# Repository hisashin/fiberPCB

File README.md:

# Getting started with fiberPCB, Fiber Laser DIY PCB

- [Why fiberPCB?](#why-fiberPCB?)
- [References](#references)
- [Required tools and materials](#all-required-tools-and-materials)
- [How to choose fiber laser](#how-to-choose-fiber-laser)
- [How to choose laminator](#how-to-choose-laminator)
- [Detailed steps to make fiberPCB by KiCAD](#detailed-steps-to-make-fiberPCB-by-KiCAD)
- [Detailed steps to make fiberPCB by EAGLE](#detailed-steps-to-make-fiberPCB-by-EAGLE)

## Why fiberPCB?

Let's compare fiberPCB with alternatives.

* Online PCB service
  * Best way as long as you can wait delivery for few days to weeks.
  * Sometimes you cannot wait. In my case, PCB of [opensource Realtime PCR](https://github.com/hisashin/Ninja-qPCR) was so complex that I have to iterate orders to integrate functions like LED control, photosensing, multiplexing and ADC.
* Chemical etching
  * Cheap but need skills for small pitches like 10 mil (0.25mm).
  * Need to drill all holes and cut contor manually after etching.
  * Harmful to the environment.
* CNC milling
  * I had [$2300 CNC designed for PCB millling](https://www.youtube.com/watch?v=cwREOBL9E-A) and noticed that required time and cares are proportionate to the complexity of the pattern.
  * You must replace end mills not to cut holes and contor after cutting patterns. Or you have to replace it every 50 meter stroke. Machine with auto tool changer is expensive. [LPKF ProtoMat S104](https://www.youtube.com/watch?v=GRow5AqFxZA) is around $30,000.
  * To cut small pitches, you cannot engrave deeply. If depth is not enough, small copper partcle may bridge the gap. I'm totally fed up with such problems.
* Commercial PCB laser machine.
  * Ridiculously expensive. "Entry model" [LPKF Photolaser ST](https://www.youtube.com/watch?v=WMgXvRwbaLw) is over $100,000.
* CO2 Laser
  * I've never tried CO2 laser etching. Please send pull request if you can compare.
  * Cannot etch metal without spraying black.
  * Focal diameter is 100 times larger and edge might be unclear at small pitches.
  
## References
* [Making fine pitch PCB prototypes with fiber laser](https://www.kurokesu.com/main/2021/01/07/making-fine-pitch-pcb-prototypes-with-fiber-laser/?fbclid=IwAR3_8MipkpVS9d9DjpUQ1I7AqjXdvbW7uQoy86yiT56GoPLZ7w0Zegjyjy0)
* [Youtubes](https://www.youtube.com/playlist?list=PLIcr1mnww28Doh5sBvfblVOn0Wxk1qtYr)
 
## All required tools and materials
* Gerber Files (Free)
* [FlatCAM](http://flatcam.org/), Gerver->CAM conveter

  Latest stable FlatCAM3.5 needs Python2.7. Beta supports Python3 but crush often on Linux. [Pip](https://pypi.org/project/flatcam/#description) install looks easy but crushed while saving projects. I recommend to use Windows or Docker Ubuntu Desktop.
  
  - [Download](https://bitbucket.org/jpcgt/flatcam/downloads/) latest installer for Windows.
  - For Linux, [dorowu/ubuntu-desktop-lxde-vnc:release-v1.2](https://hub.docker.com/layers/dorowu/ubuntu-desktop-lxde-vnc/release-v1.2/images/sha256-54af3af44929d8337562448a122f32ce3ba35d8ae9aefe1365f1660d84b1792a?context=explore) is easiest.
  
   ```
   // Run this command in your terminal
   docker run -d -v (where you exported gerbers):/gerbers -v (somewhere to save flatcam projects):/projects -it --name flatcam -p 6080:80 -p 5901:5900  -e VNC_PASSWORD=password -v /dev/shm:/dev/shm dorowu/ubuntu-desktop-lxde-vnc:release-v1.2
   // My case
   docker run -d -v ~/github/fiberPCB/kicad/fiberPCB:/gerbers -v ~/github/fiberPCB/flatcam:/projects -it --name flatcam -p 6080:80 -p 5901:5900  -e VNC_PASSWORD=password -v /dev/shm:/dev/shm dorowu/ubuntu-desktop-lxde-vnc:release-v1.2
   
   // Connect VNC to vnc://localhost:5901, run these commands in Ubuntu terminal not yours.
   apt-get -y update
   apt-get -y install sudo wget git unzip
    
   //git clone https://bitbucket.org/jpcgt/flatcam <- it was also 3.5 when I tried on 2021 Jan 25
   wget https://bitbucket.org/jpcgt/flatcam/downloads/FlatCAM-8.5.zip
   unzip FlatCAM-8.5.zip
   cd FlatCAM-8.5
   sh setup_ubuntu.sh
   python FlatCAM.py
   ```

  - [dorowu/ubuntu-desktop-lxde-vnc](https://hub.docker.com/r/dorowu/ubuntu-desktop-lxde-vnc/):latest --- I couldn't install python-qt4.
  - [queeno/docker-ubuntu-desktop](https://github.com/queeno/docker-ubuntu-desktop):latest. --- It worked but app resolution was lowest.
  - Want to try FlatCAM nightly build in Python3? Here is how to install.
  
   ```
   python3 -V (3.5)
   // It was 3.5 for me and upgrade to 3.8 was needed in later step. skip here if yours is 3.8
   add-apt-repository ppa:deadsnakes/ppa
   apt-get -y update
   apt-get -y install python3.8
   update-alternatives --install /usr/bin/python3 python3 /usr/bin/python3.5 1
   update-alternatives --install /usr/bin/python3 python3 /usr/bin/python3.8 2
   update-alternatives --config python3 (Choose python3.8)
   python3 -V
   apt install -y python3.8-distutils python-setuptools python3-pip
   pip3 -V (8.1.1)
   apt remove python3-pip
   python3.8 -m easy_install pip
   pip -V (21.0)
 
   apt-get -y update
   apt-get -y install python3-pip python-setuptools sudo wget
   wget https://bitbucket.org/jpcgt/flatcam/downloads/FlatCAM_beta_8.994_sources.zip
   unzip FlatCAM_beta_8.994_sources.zip
   cd FlatCAM_beta_8.994_sources
   sh setup_ubuntu.sh
   python3 FlatCAM.py
   ```
   
* [EZCAD](https://www.litlaser.com/ezcad), laser controller
* Fiber Laser
* Laminator
* UV illuminator
* Dry film
  * I first thought that Kapton film can replace it but that would be wrong.
* [FR-4](https://en.wikipedia.org/wiki/FR-4)

My case in Tokyo Japan :
| Item                | Price         | Shipping     | Comment |
| ------------------- |:-------------:| ------------:| ------------:|
| [Fiber Laser](https://www.aliexpress.com/item/32974751052.html?spm=a2g0s.9042311.0.0.65f44c4dIleBKp&fbclid=IwAR10NMvGiH47895B0QpRRJNL5SNHvLvtUy33UhqqUZfuPdR8BVw_eg-WCHc)         | $1,837.44     | $249.81 | 20W JPT 200x200mm DHL8-16days |
| [Laminator](https://www.lami-corporation.co.jp/archives/products/leon13dx/)           | $10.64        | $11.12       | Got $1800 worth one as junk. Replaced blown fuse:wink: |
| [UV illuminator](https://www.amazon.co.jp/gp/product/B07HFRDK3V/ref=ppx_yo_dt_b_asin_title_o02_s00?ie=UTF8&psc=1&fbclid=IwAR2NO4W7daOl4TgFSwwDDsZGD15Jek28WylPpzhUsRBBjHX5G8EQiuQLUwU)      | $4.73         | $0           | I will line them up for larger PCB |
| [Dry film](https://www.amazon.co.jp/gp/product/B01NCS88LU/ref=ppx_yo_dt_b_asin_title_o05_s01?ie=UTF8&psc=1&fbclid=IwAR3ORckfPM1z7tKVWN8LTQ-CgsBqjpBLfcwR8V2A0jhZy2ZhwNkz0N1GbfY)          | $19.15        | $0           | VANTIYAUS Zp00088(5m x 30cm) |
| [FR-4](https://www.sengoku.co.jp/mod/sgk_cart/detail.php?code=EEHD-4BPE)                | $1.64         | $0           | 1.6t x 75 x 100mm |
| Total               | $1873.6       | $260.93      |  $2395.46 include shippings |

## How to choose fiber laser
 // TODO Stronger/Wider is not always better

## How to choose laminator
 // TODO List confirmed to support 1.6mm thickness

## Detailed steps to make fiberPCB by KiCAD
 1. Design PCB as usual
   
 2. Export Gerber Files
   - **File/Plot** and check F.Cu, F.Paste, F.Mask and Edge.Cuts then **Plot**
   
   - **Generate Drill Files... / Generate Drill File**
   
 3. Convert Gerber
   - **File / Open Gerbers** and select all gerbers exported at prior step.
   
 4. Convert CAM
 5. Cut patterns
 6. Print solder mask
 7. Open pads
 8. Cut holes and contor

## Detailed steps to make fiberPCB by EAGLE

// TODO

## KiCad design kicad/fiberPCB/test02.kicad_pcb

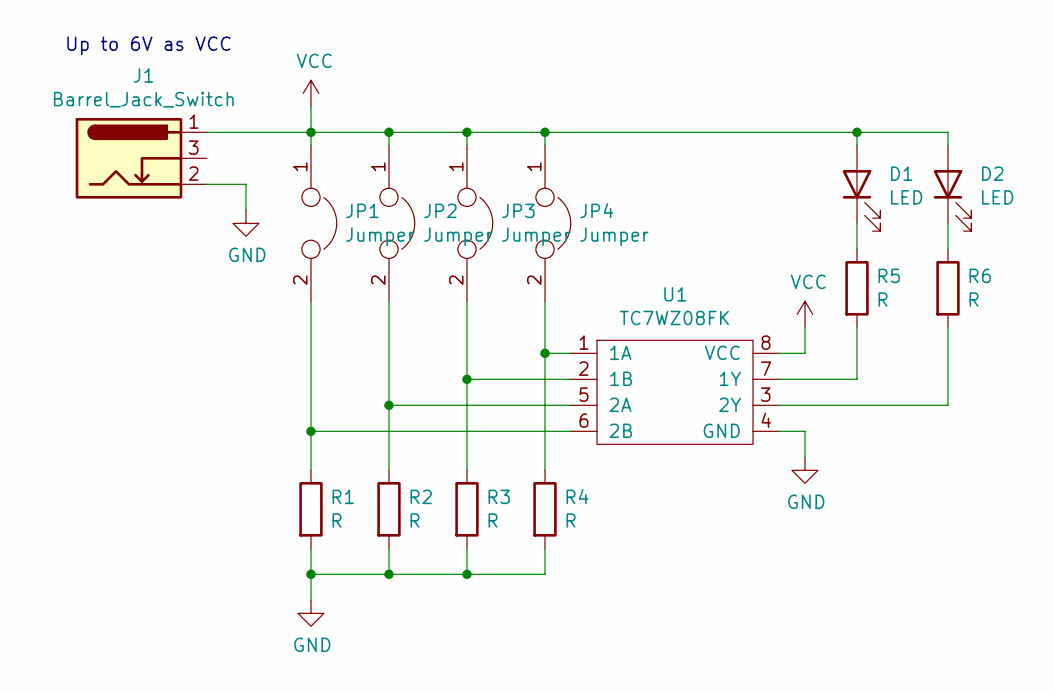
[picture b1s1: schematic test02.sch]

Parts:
D1, D2: LED; LED_D5.0mm
J1: Barrel_Jack_Switch; BarrelJack_Horizontal
JP1, JP3: Jumper; SolderJumper-2_P1.3mm_Open_Pad1.0x1.5mm
JP2: Jumper; SolderJumper-2_P1.3mm_Open_RoundedPad1.0x1.5mm
JP4: Jumper; SolderJumper-2_P1.3mm_Open_TrianglePad1.0x1.5mm
R1, R3, R5: R; R_0603
R2, R4, R6: R; R_0603_HandSoldering
U1: TC7WZ08FK; SOP50P310X90-8N

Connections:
GND: J1.2, R1.2, R2.2, R3.2, R4.2, U1.4 (GND)
unnamed: D1.1 (K), R5.1
unnamed: D2.1 (K), R6.1
unnamed: JP1.2, R1.1, U1.6 (2B)
unnamed: JP2.2, R2.1, U1.5 (2A)
unnamed: JP3.2, R3.1, U1.2 (1B)
unnamed: JP4.2, R4.1, U1.1 (1A)
unnamed: R5.2, U1.7 (1Y)
unnamed: R6.2, U1.3 (2Y)
VCC: D1.2 (A), D2.2 (A), J1.1, JP1.1, JP2.1, JP3.1, JP4.1, U1.8 (VCC)

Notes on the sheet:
Up to 6V as VCC

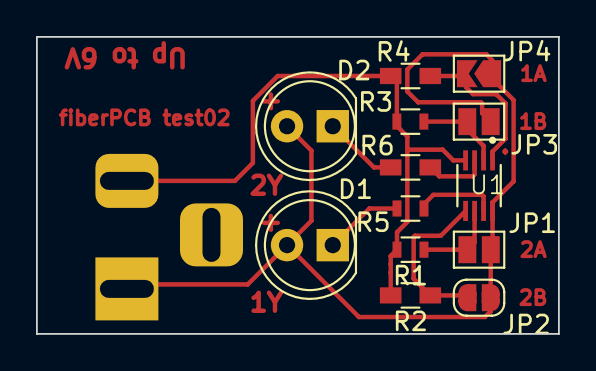
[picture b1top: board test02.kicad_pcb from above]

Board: 2 copper layers, 29.0 x 16.5 mm, 14 parts (1 on the bottom side), 10 nets.

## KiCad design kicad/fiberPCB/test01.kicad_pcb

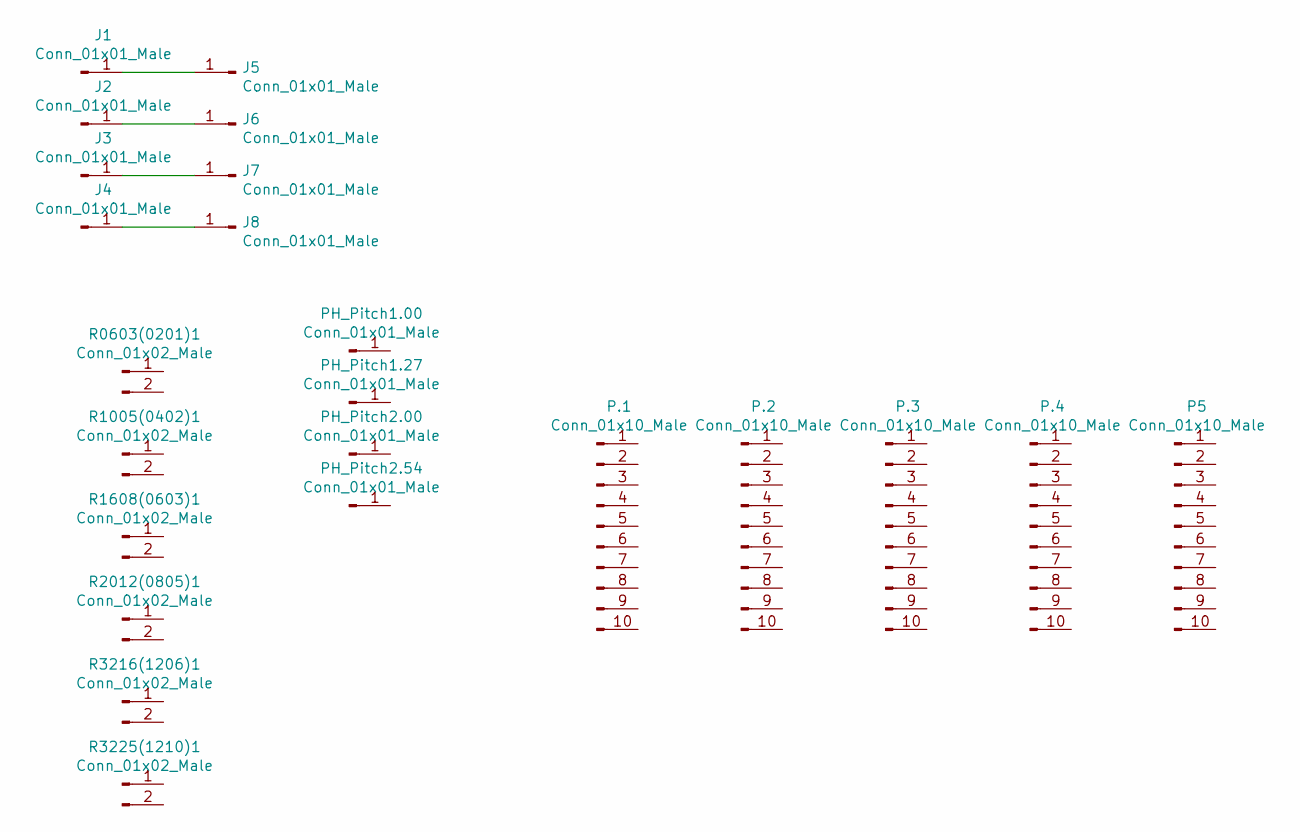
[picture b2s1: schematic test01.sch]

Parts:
J1, J2, J3, J4, J5, J6, J7, J8: Conn_01x01_Male; Checkpoint
P5: Conn_01x10_Male; SOIC-10-1.0-gap0.4
P.1: Conn_01x10_Male; SOIC-10-0.4-gap0.2
P.2: Conn_01x10_Male; SOIC-10-0.5-gap0.25
P.3: Conn_01x10_Male; SOIC-10-0.65-gap0.3
P.4: Conn_01x10_Male; SOIC-10-0.8-gap0.35
PH_Pitch1.00: Conn_01x01_Male; Pin_Header_Straight_1x01_Pitch1.00mm
PH_Pitch1.27: Conn_01x01_Male; Pin_Header_Straight_1x01_Pitch1.27mm
PH_Pitch2.00: Conn_01x01_Male; Pin_Header_Straight_1x01_Pitch2.00mm
PH_Pitch2.54: Conn_01x01_Male; Pin_Header_Straight_1x01_Pitch2.54mm
R0603(0201)1: Conn_01x02_Male; R_0201
R1005(0402)1: Conn_01x02_Male; R_0402
R1608(0603)1: Conn_01x02_Male; R_0603
R2012(0805)1: Conn_01x02_Male; R_0805
R3216(1206)1: Conn_01x02_Male; R_1206
R3225(1210)1: Conn_01x02_Male; R_1210

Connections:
unnamed: J1.1, J5.1
unnamed: J2.1, J6.1
unnamed: J3.1, J7.1
unnamed: J4.1, J8.1

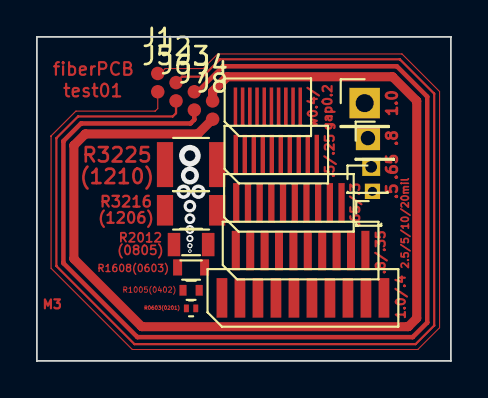
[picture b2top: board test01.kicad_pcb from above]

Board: 2 copper layers, 23.0 x 18.0 mm, 23 parts (0 on the bottom side), 4 nets.

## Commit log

2021-01-21 add test pattern
2021-01-21 add image of step1
2021-01-21 made test01 pattern
2021-01-21 rewire test01 pattern
2021-01-22 describe steps
2021-01-22 add step2_drilll
2021-01-22 update test02
2021-01-23 add step3
